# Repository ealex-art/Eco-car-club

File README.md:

# Eco-car-club
First PCB design
First PCB design, with one error being Zone [GND] on B.Cu, Priority 0
Enoch's change test #1
Enoch's change test #2

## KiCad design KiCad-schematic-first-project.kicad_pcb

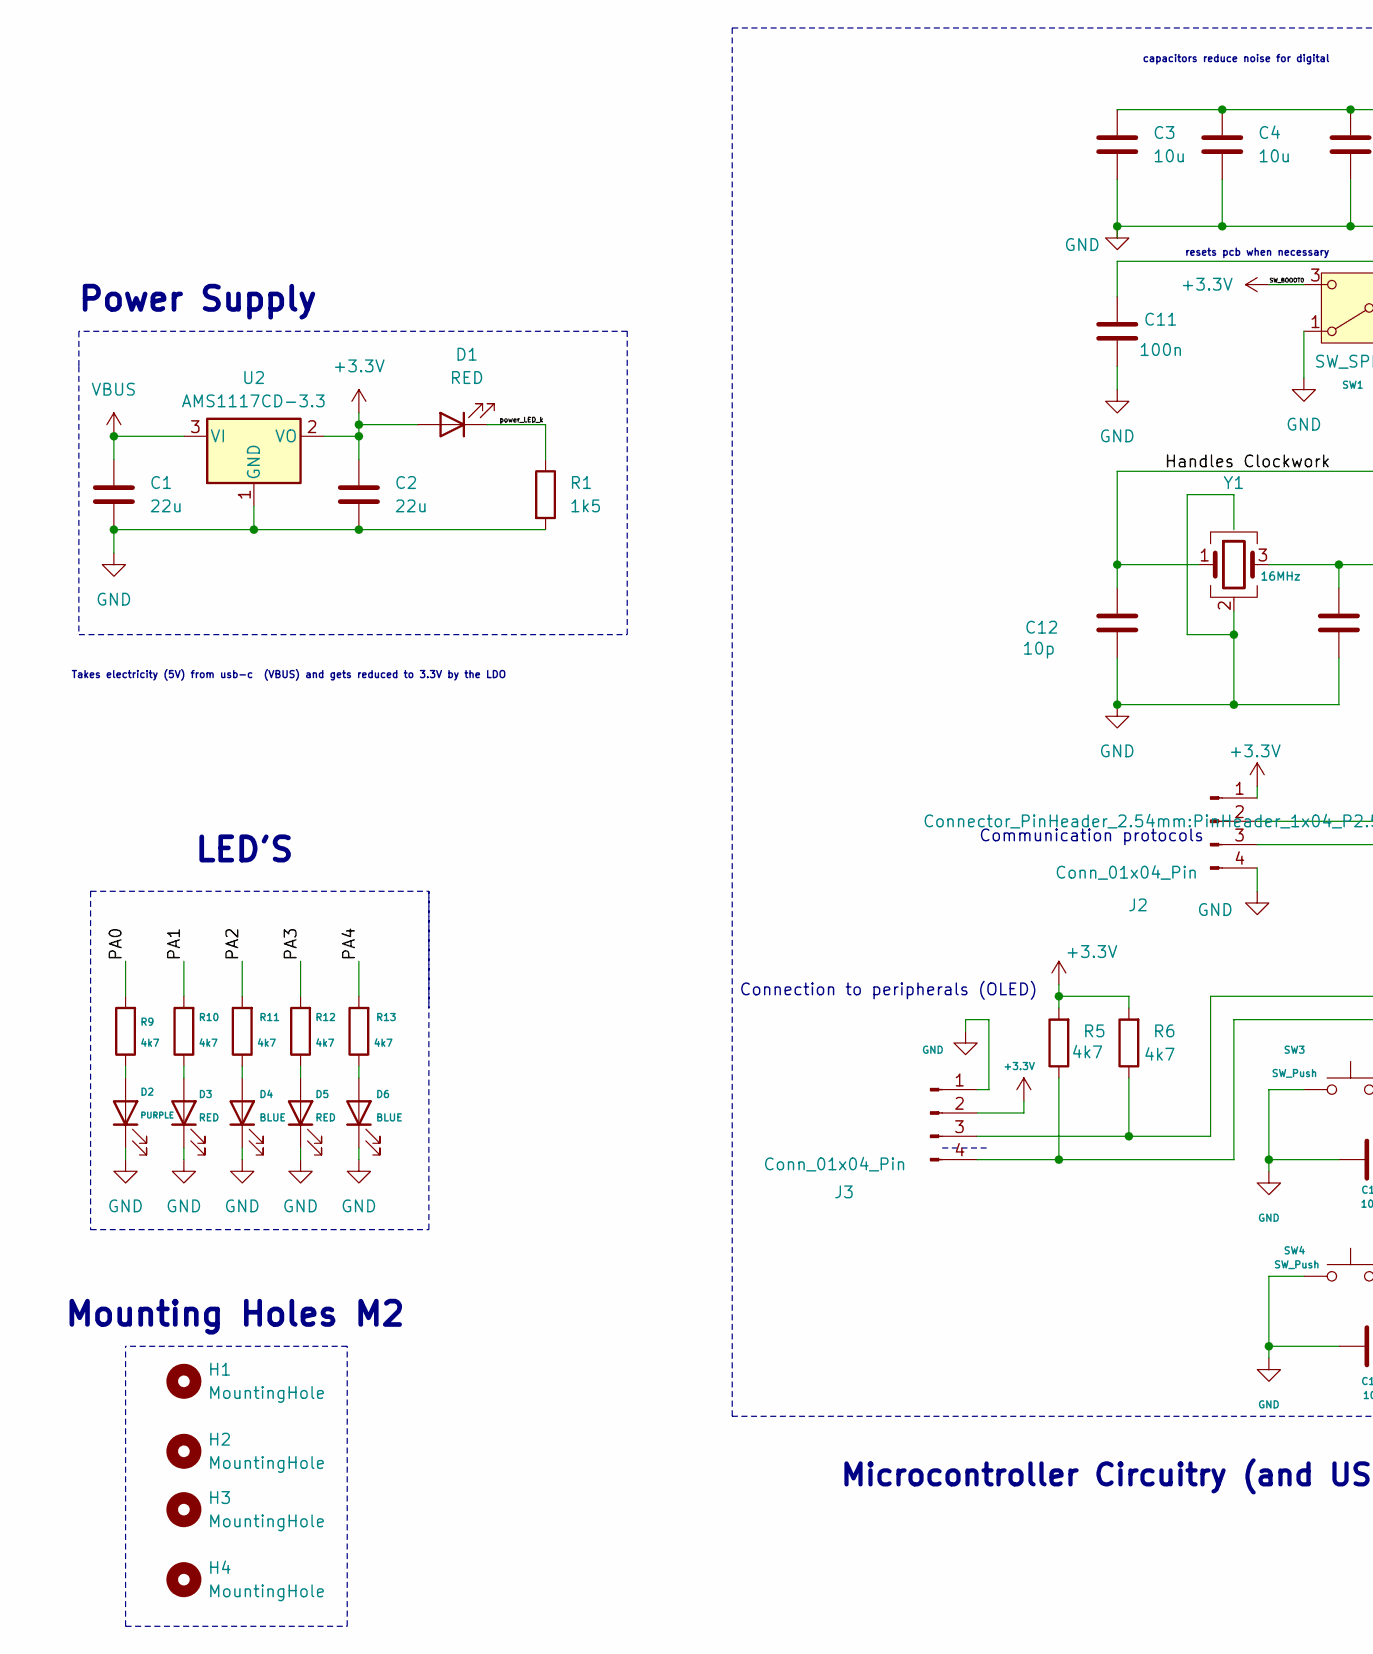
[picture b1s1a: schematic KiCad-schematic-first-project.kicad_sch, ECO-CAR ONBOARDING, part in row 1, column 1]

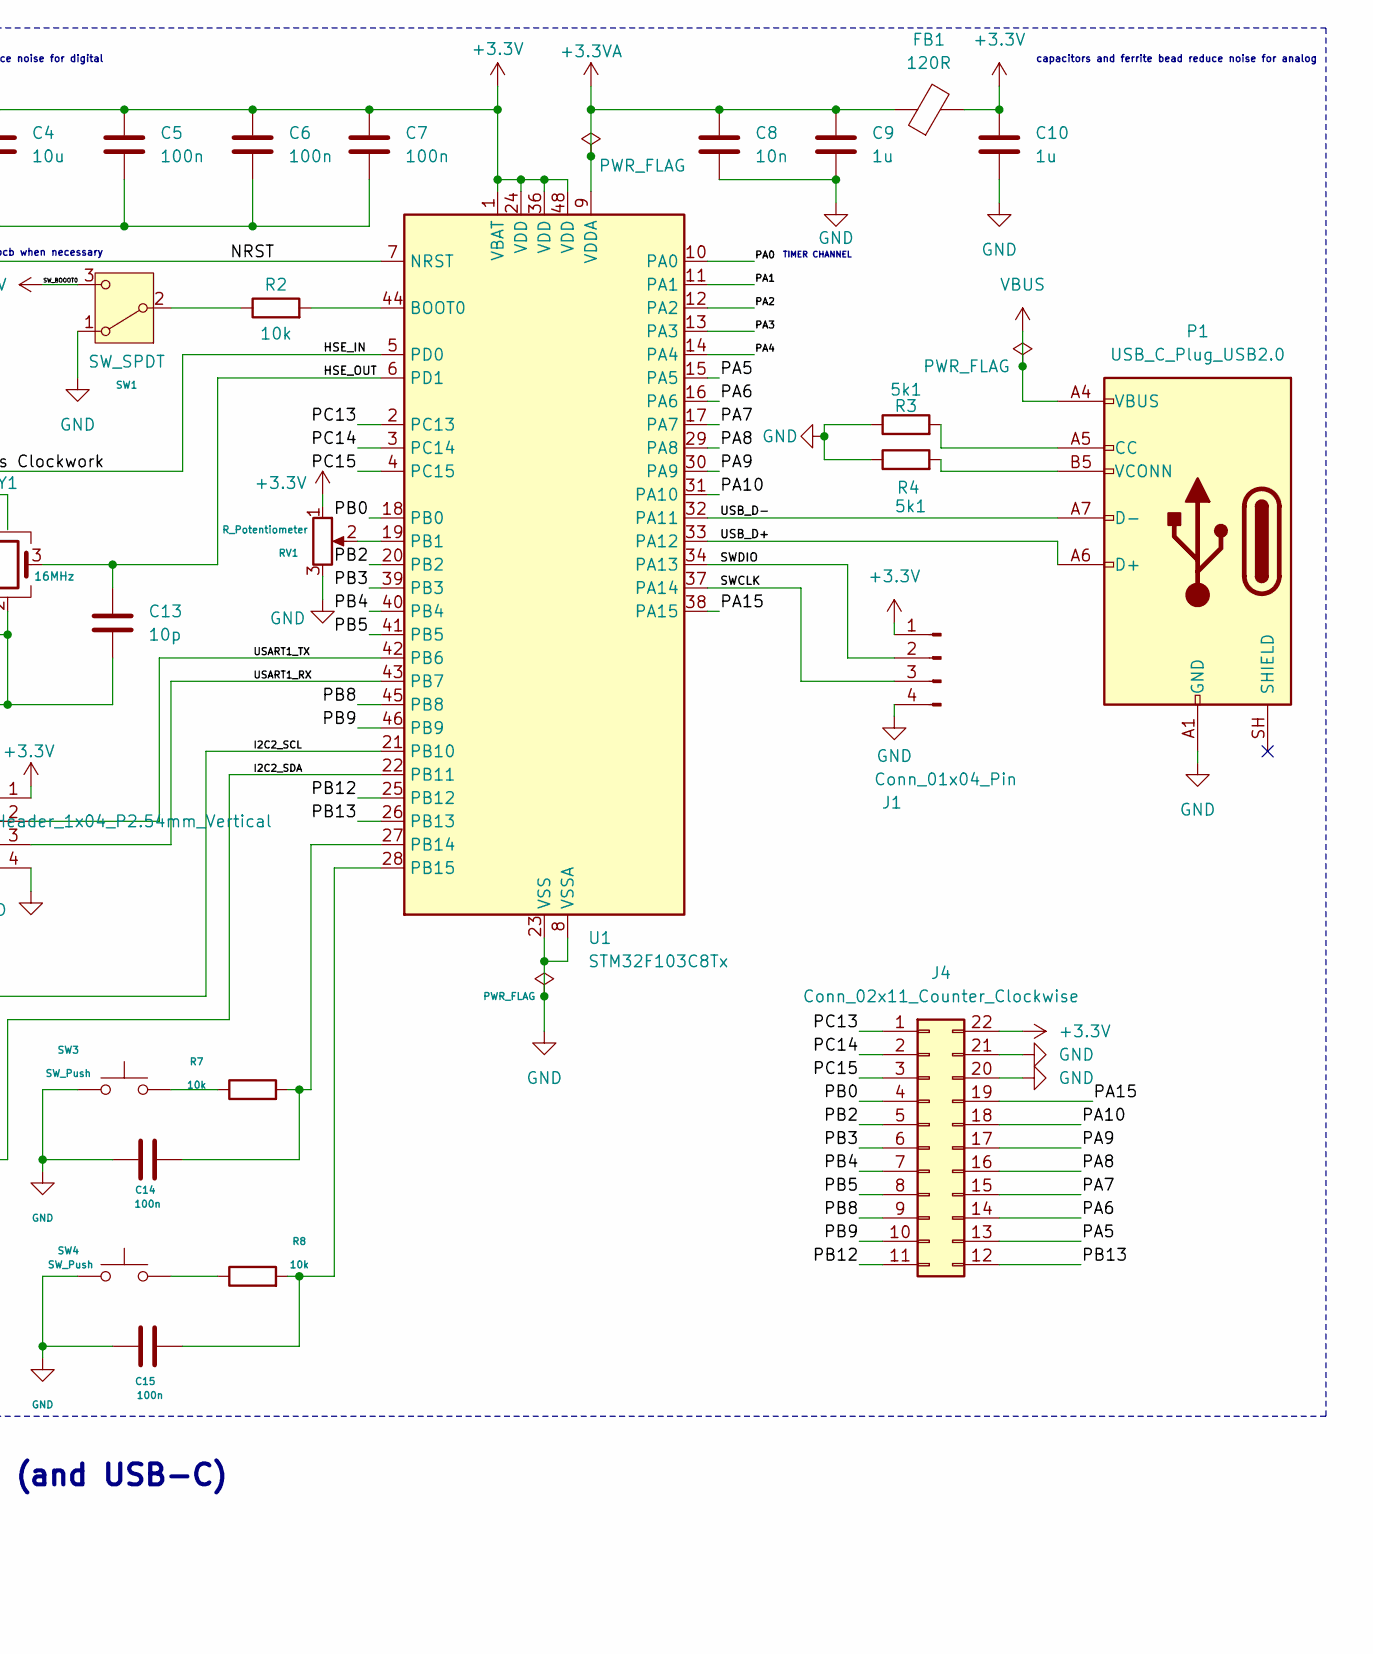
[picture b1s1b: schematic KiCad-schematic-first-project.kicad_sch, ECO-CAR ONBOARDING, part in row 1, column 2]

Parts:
C1, C2: 22u; C_0603_1608Metric
C3, C4: 10u; C_0603_1608Metric
C5, C6, C7, C11, C14, C15: 100n; C_0603_1608Metric
C8: 10n; C_0603_1608Metric
C9, C10: 1u; C_0603_1608Metric
C12, C13: 10p; C_0603_1608Metric
D1, D3, D5: RED; LED_0603_1608Metric
D2: PURPLE; LED_0603_1608Metric
D4, D6: BLUE; LED_0603_1608Metric
FB1: 120R; L_0603_1608Metric
H1, H2, H3, H4: MountingHole; MountingHole_2.2mm_M2
J1, J2, J3: Conn_01x04_Pin; PinHeader_1x04_P2.54mm_Vertical
J4: Conn_02x11_Counter_Clockwise; PinHeader_2x11_P2.54mm_Vertical
P1: USB_C_Plug_USB2.0; USB_C_Receptacle_HRO_TYPE-C-31-M-12
R1: 1k5; R_0603_1608Metric
R2, R7, R8: 10k; R_0603_1608Metric
R3, R4: 5k1; R_0603_1608Metric
R5, R6, R9, R10, R11, R12, R13: 4k7; R_0603_1608Metric
RV1: R_Potentiometer; Potentiometer_Bourns_3386W_Horizontal
SW1: SW_SPDT; SW_SPDT_Shouhan_MSK12C02
SW3, SW4: SW_Push; SW_PUSH_6mm_H5mm
U1: STM32F103C8Tx; LQFP-48_7x7mm_P0.5mm
U2: AMS1117CD-3.3; SOT-223-3_TabPin2
Y1: 16MHz; Crystal_SMD_3225-4Pin_3.2x2.5mm

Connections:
+3.3V: C2.1, C3.1, C4.1, C5.1, C6.1, C7.1, C10.1, D1.2 (A), FB1.2, J1.1, J2.1, J3.2, J4.22, R5.2, R6.2, RV1.1, SW1.3 (C), U1.1 (VBAT), U1.24 (VDD), U1.36 (VDD), U1.48 (VDD), U2.2 (VO)
+3.3VA: C8.1, C9.1, FB1.1, U1.9 (VDDA)
/HSE_IN: C12.1, U1.5 (PD0), Y1.1
/HSE_OUT: C13.1, U1.6 (PD1), Y1.3
/I2C2_SCL: J3.3, R6.1, U1.21 (PB10)
/I2C2_SDA: J3.4, R5.1, U1.22 (PB11)
/NRST: C11.1, U1.7 (NRST)
/PA0: R9.2, U1.10 (PA0)
/PA1: R10.2, U1.11 (PA1)
/PA2: R11.2, U1.12 (PA2)
/PA3: R12.2, U1.13 (PA3)
/PA4: R13.2, U1.14 (PA4)
/PA5: J4.13, U1.15 (PA5)
/PA6: J4.14, U1.16 (PA6)
/PA7: J4.15, U1.17 (PA7)
/PA8: J4.16, U1.29 (PA8)
/PA9: J4.17, U1.30 (PA9)
/PA10: J4.18, U1.31 (PA10)
/PA15: J4.19, U1.38 (PA15)
/PB0: J4.4, U1.18 (PB0)
/PB2: J4.5, U1.20 (PB2)
/PB3: J4.6, U1.39 (PB3)
/PB4: J4.7, U1.40 (PB4)
/PB5: J4.8, U1.41 (PB5)
/PB8: J4.9, U1.45 (PB8)
/PB9: J4.10, U1.46 (PB9)
/PB12: J4.11, U1.25 (PB12)
/PB13: J4.12, U1.26 (PB13)
/PC13: J4.1, U1.2 (PC13)
/PC14: J4.2, U1.3 (PC14)
/PC15: J4.3, U1.4 (PC15)
/SWCLK: J1.3, U1.37 (PA14)
/SWDIO: J1.2, U1.34 (PA13)
/USART1_RX: J2.3, U1.43 (PB7)
/USART1_TX: J2.2, U1.42 (PB6)
/USB_D+: P1.A6 (D+), U1.33 (PA12)
/USB_D-: P1.A7 (D-), U1.32 (PA11)
/power_LED_k: D1.1 (K), R1.1
GND: C1.2, C2.2, C3.2, C4.2, C5.2, C6.2, C7.2, C8.2, C9.2, C10.2, C11.2, C12.2, C13.2, C14.1, C15.1, D2.1 (K), D3.1 (K), D4.1 (K), D5.1 (K), D6.1 (K), J1.4, J2.4, J3.1, J4.20, J4.21, P1.A1 (GND), P1.A12 (GND), P1.B1 (GND), P1.B12 (GND), R1.2, R3.1, R4.1, RV1.3, SW1.1 (A), SW3.1, SW4.1, U1.8 (VSSA), U1.23 (VSS), U1.35 (VSS), U1.47 (VSS), U2.1 (GND), Y1.2 (G), Y1.4 (G)
unnamed: D2.2 (A), R9.1
unnamed: D3.2 (A), R10.1
unnamed: D4.2 (A), R11.1
unnamed: D5.2 (A), R12.1
unnamed: D6.2 (A), R13.1
unnamed: P1.A5 (CC), R3.2
unnamed: P1.B5 (VCONN), R4.2
unnamed: R7.1, SW3.2
unnamed: R8.1, SW4.2
unnamed: R2.1, SW1.2 (B)
unnamed: R2.2, U1.44 (BOOT0)
unnamed: RV1.2, U1.19 (PB1)
unnamed: C14.2, R7.2, U1.27 (PB14)
unnamed: C15.2, R8.2, U1.28 (PB15)
VBUS: C1.1, P1.A4 (VBUS), P1.A9 (VBUS), P1.B4 (VBUS), P1.B9 (VBUS), U2.3 (VI)

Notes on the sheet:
Power Supply
capacitors and ferrite bead reduce noise for analog
Microcontroller Circuitry (and USB-C)
Connection to peripherals (OLED)
LED'S
TIMER CHANNEL
resets pcb when necessary
Takes electricity (5V) from usb-c (VBUS) and gets reduced to 3.3V by the LDO
Communication protocols
capacitors reduce noise for digital
Mounting Holes M2

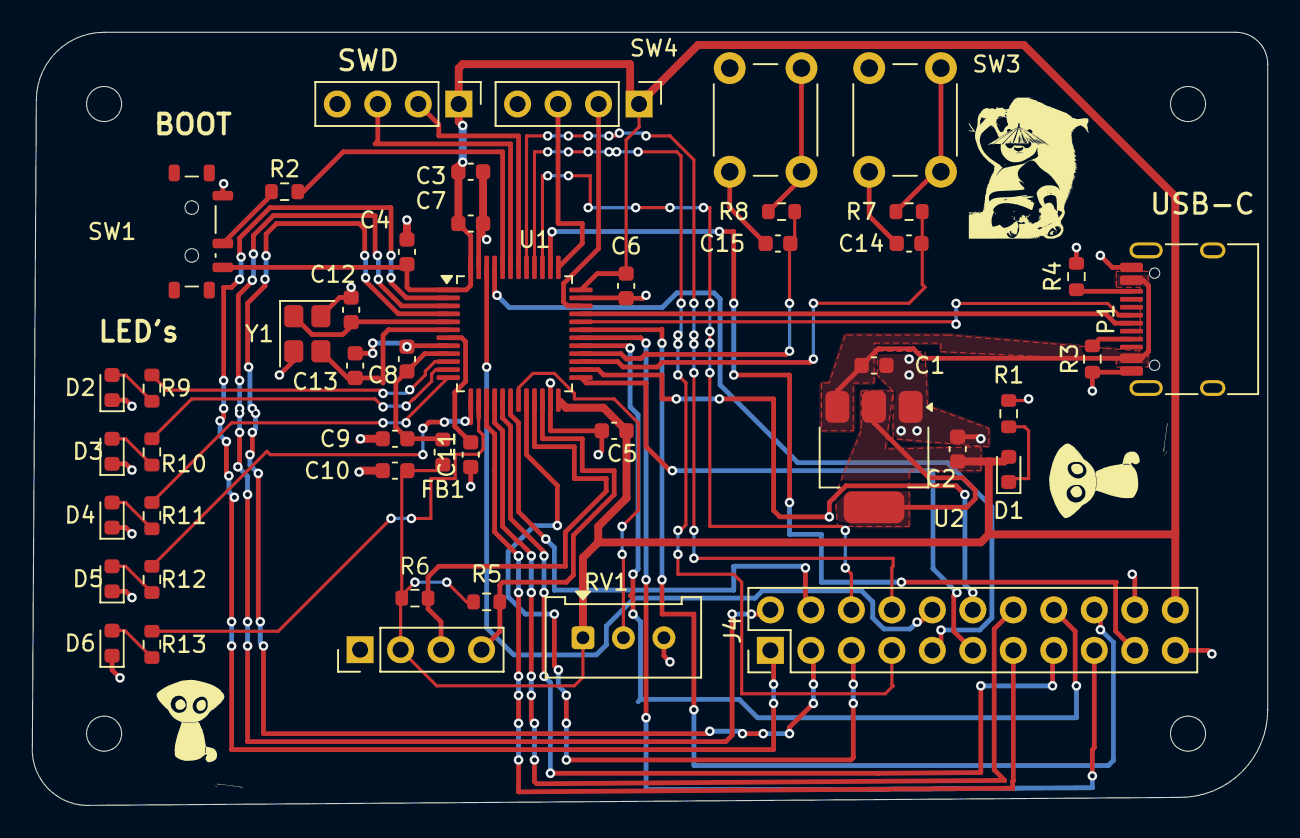
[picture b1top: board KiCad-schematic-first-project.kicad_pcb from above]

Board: 2 copper layers, 77.5 x 48.5 mm, 51 parts (0 on the bottom side), 54 nets.
